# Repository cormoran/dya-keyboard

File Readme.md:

#  DYA Split Keyboard

## Features

- Controller: RP2040-zero (QMK) and XAIO NRF52840 plus (ZMK)
  - ZMK firmware is not available yet, since XAIO NRF52840 plus cannot be used in Japan for now.
- Layout: US and JIS
- Switch: Cherry MX compatible, hotswappable
- LED x 12 (left 4, right 4 + 4 indicator)
- PMW3610 low power trackball sensor
- Optional features by soldering additional parts
  - Lipo battery support for XAIO
  - AAA battery (1.2V NiMH or 1.5V) support

## Build Guide

[V1.0 部品取り付け済み基板（日本語）](./hardware/dya-v1/build-guide/pcba/Readme-ja.md)

## Firmware

Pre-built QMK firmware is available in latest build's artifact section in [this github actions](https://github.com/cormoran/dya-keyboard/actions/workflows/main.yml).

Three binaries (via, us, jis) are zipped in `dya_qmk_latest.zip`. `via` binary supports [VIA](https://www.usevia.app/) and [Remap](https://remap-keys.app/) to change keymapping. Keyboard definition json for VIA is available in [`./firmware/qmk/keybaords/dya/dya-via.json`](https://github.com/cormoran/dya-keyboard/blob/main/firmware/qmk/keyboards/dya/dya-via.json).

## Gallery

- Keycap: [acid-caps](https://keeb-on.com/collections/acid-caps) or no-brand white cap
- Trackball: 34mm

### US Layout setup

#### LED decoration and indicators

### JIS Layout setup

### Schematic

## Shop

Available in https://cormoran707.booth.pm/items/6705756

## License

- QMK firmware (./firmware/qmk_firmware/\*): Inherits its license. Majority of them are under GPLv2. See its own repository.
- DYA logo  (./img/dya.svg): All rights reserved.
- Other keyboard pictures under ./img: CC BY
- Hardware
  - kicad library (./hardware/kicad_library/\*) and sch (\*.kicad_sch): MIT
  - PCB (\*.kicad_pcb): CC BY-NC
  - Case data (\*.stl): CC BY

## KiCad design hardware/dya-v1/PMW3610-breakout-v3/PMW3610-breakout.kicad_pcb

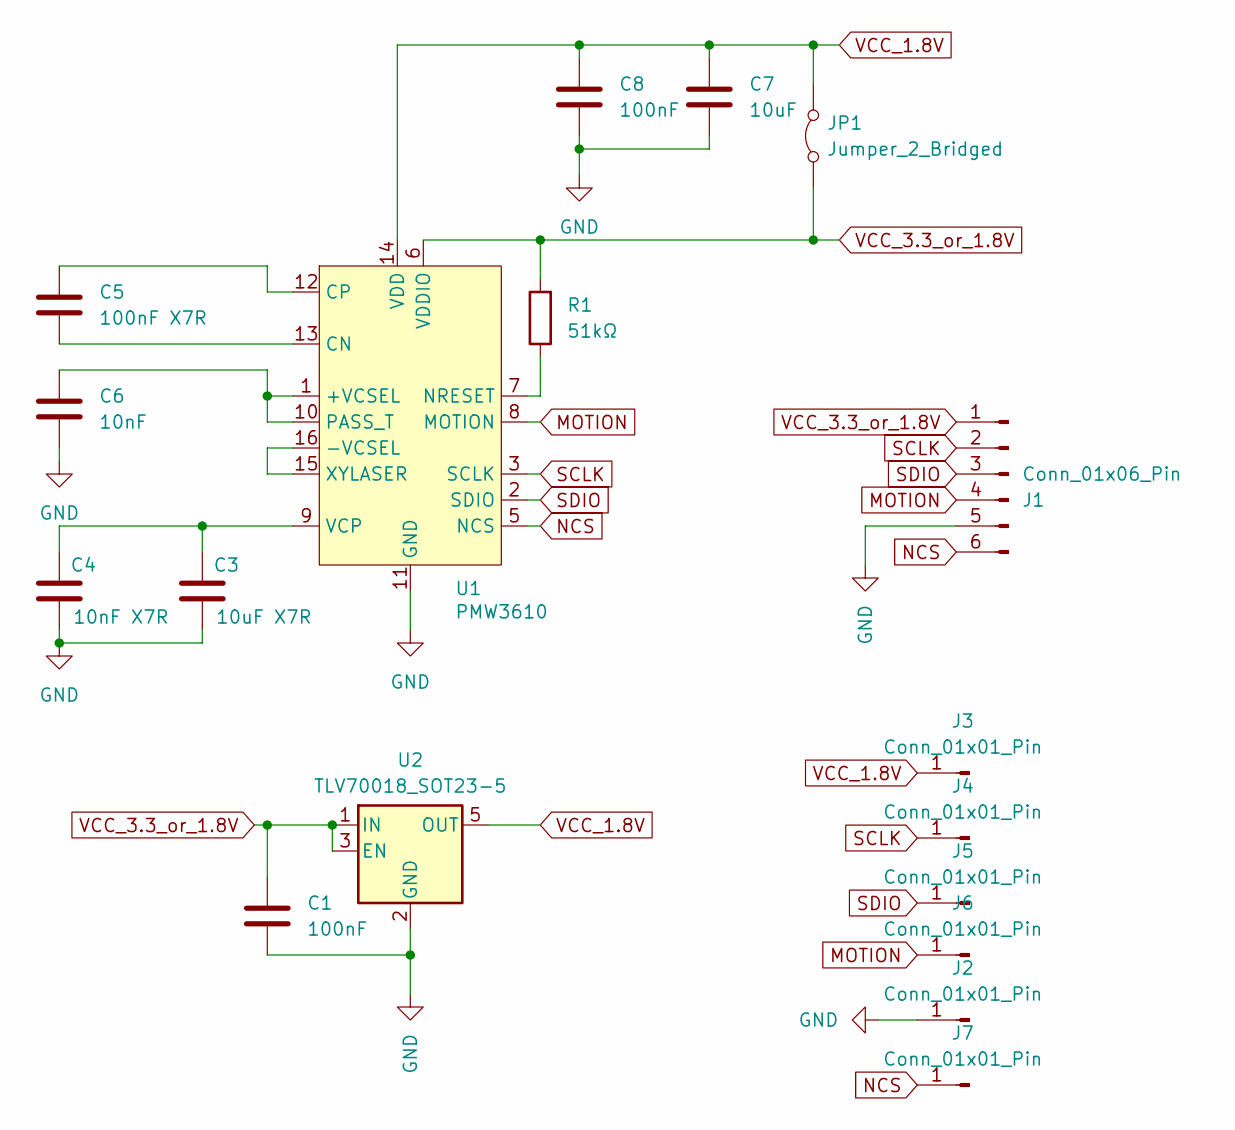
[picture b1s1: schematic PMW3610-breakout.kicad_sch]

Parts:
C1, C8: 100nF; C_0603_1608Metric; LCSC C14663
C3: 10uF X7R; C_0603_1608Metric; LCSC C19702
C4: 10nF X7R; C_0603_1608Metric; LCSC C57112
C5: 100nF X7R; C_0603_1608Metric; LCSC C14663
C6: 10nF; C_0603_1608Metric; LCSC C57112
C7: 10uF; C_0603_1608Metric; LCSC C19702
J1: Conn_01x06_Pin; JUSHUO-AFH34-S06FIA-1H; LCSC C5139821
J2, J3, J4, J5, J6, J7: Conn_01x01_Pin; TestPoint_Pad_D1.0mm
JP1: Jumper_2_Bridged; SolderJumper-2_P1.3mm_Open_RoundedPad1.0x1.5mm
R1: 51kΩ; R_0603_1608Metric; LCSC C23196
U1: PMW3610; PMW3610DM-SUDU 16Pin
U2: TLV70018_SOT23-5; SOT-23-5

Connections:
GND: C1.2, C3.2, C4.2, C6.2, C7.2, C8.2, J1.5, J2.1, U1.11 (GND), U2.2 (GND)
MOTION: J1.4, J6.1, U1.8 (MOTION)
NCS: J1.6, J7.1, U1.5 (NCS)
unnamed: C6.1, U1.1 (+VCSEL), U1.10 (PASS_T)
unnamed: U1.15 (XYLASER), U1.16 (-VCSEL)
unnamed: C5.2, U1.13 (CN)
unnamed: C5.1, U1.12 (CP)
unnamed: R1.1, U1.7 (NRESET)
unnamed: C3.1, C4.1, U1.9 (VCP)
SCLK: J1.2, J4.1, U1.3 (SCLK)
SDIO: J1.3, J5.1, U1.2 (SDIO)
VCC_1.8V: C7.1, C8.1, J3.1, JP1.2 (B), U1.14 (VDD), U2.5 (OUT)
VCC_3.3_or_1.8V: C1.1, J1.1, JP1.1 (A), R1.2, U1.6 (VDDIO), U2.1 (IN), U2.3 (EN)

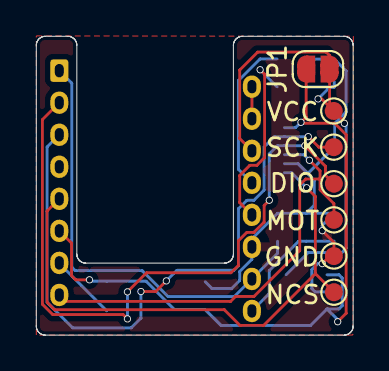
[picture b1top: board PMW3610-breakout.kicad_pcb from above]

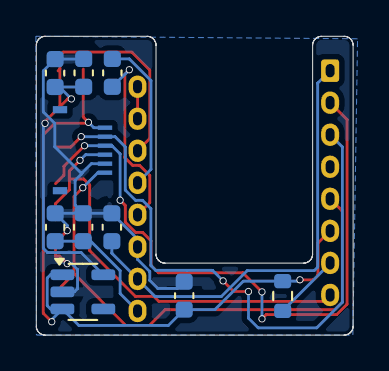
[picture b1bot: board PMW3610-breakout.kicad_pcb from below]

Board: 2 copper layers, 17.6 x 16.6 mm, 18 parts (10 on the bottom side), 13 nets.

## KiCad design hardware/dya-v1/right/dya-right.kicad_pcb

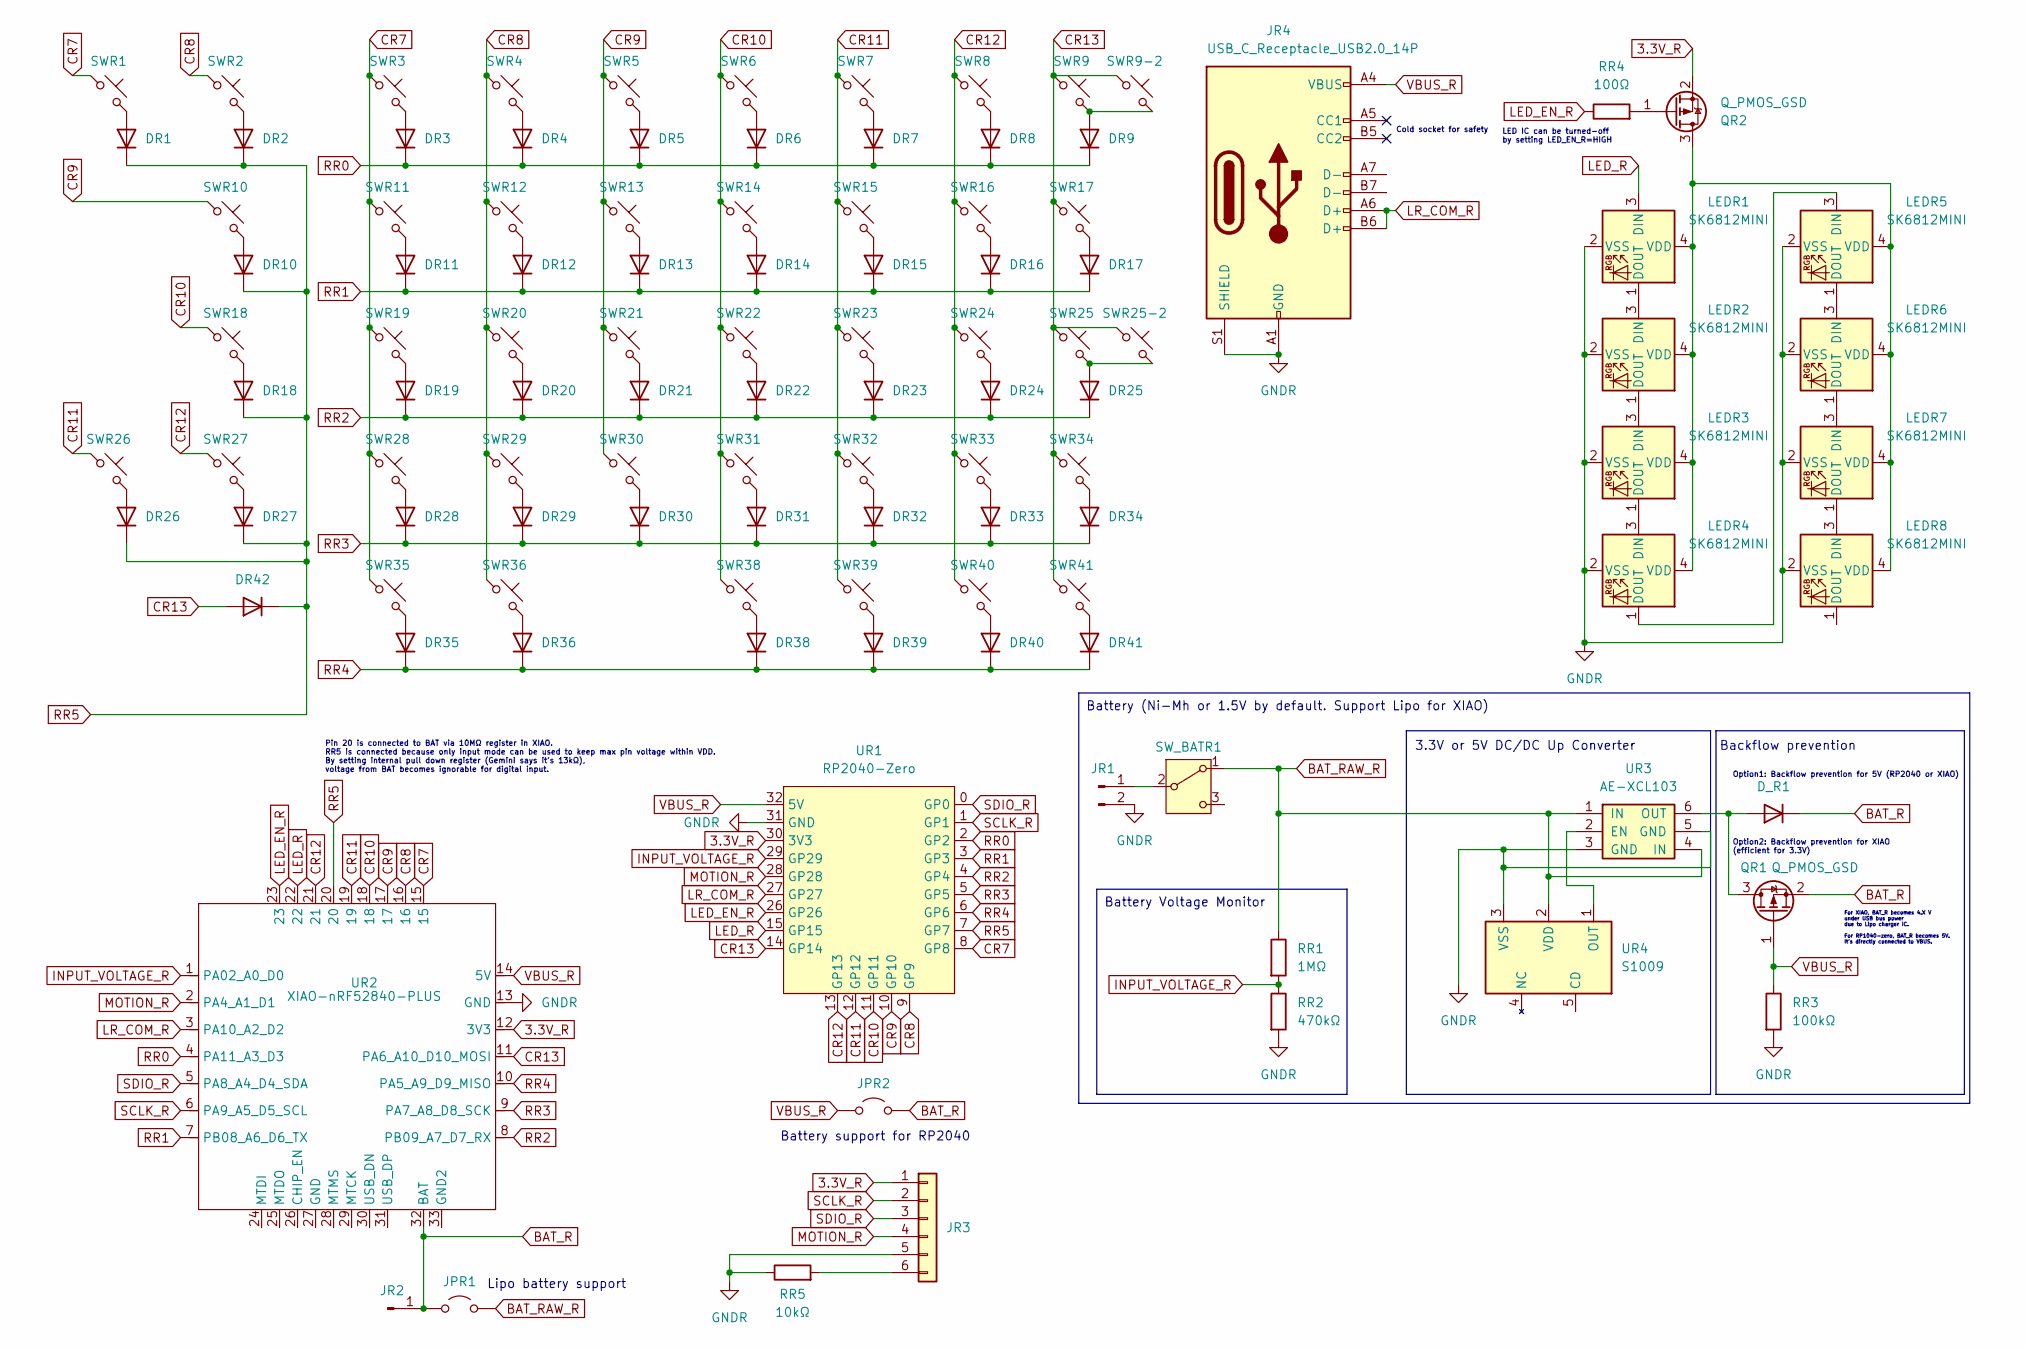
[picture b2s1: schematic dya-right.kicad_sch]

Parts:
DR1, DR2, DR3, DR4, DR5, DR6, DR7, DR8, DR9, DR10, DR11, DR12, DR13, DR14, DR15, DR16, DR17, DR18, DR19, DR20, DR21, DR22, DR23, DR24, DR25, DR26, DR27, DR28, DR29, DR30, DR31, DR32, DR33, DR34, DR35, DR36, DR38, DR39, DR40, DR41, DR42: D; D_SOD-123; LCSC C81598
D_R1: D; D_SOD-123; LCSC C81598
JPR1, JPR2: Jumper_2_Open; SolderJumper-2_P1.3mm_Open_RoundedPad1.0x1.5mm
JR1: Conn_01x02_Pin; JST_ZH_B2B-ZR_1x02_P1.50mm_Vertical
JR2: Conn_01x01_Pin; SolderWirePad_1x01_SMD_1x2mm
JR3: Conn_01x04; JUSHUO-AFH34-S06FIA-1H; LCSC C5139821
JR4: USB_C_Receptacle_USB2.0_14P; USB_C_Receptacle_G-Switch_GT-USB-7010ASV; LCSC C2927038
LEDR1, LEDR2, LEDR3, LEDR4, LEDR5, LEDR6, LEDR7, LEDR8: SK6812MINI; LED_SK6812MINI-E_BL; LCSC C5149201
QR1, QR2: Q_PMOS_GSD; SOT-23; LCSC C15127
RR1: 1MΩ; R_0805_2012Metric; LCSC C17514
RR2: 470kΩ; R_0805_2012Metric; LCSC C17709
RR3: 100kΩ; R_0805_2012Metric; LCSC C149504
RR4: 100Ω; R_0805_2012Metric; LCSC C17408
RR5: 10kΩ; R_0805_2012Metric; LCSC C17414
SWR1, SWR2, SWR3, SWR4, SWR5, SWR6, SWR7, SWR8, SWR9, SWR10, SWR11, SWR12, SWR13, SWR14, SWR15, SWR16, SWR17, SWR18, SWR19, SWR20, SWR21, SWR22, SWR23, SWR24, SWR26, SWR27, SWR28, SWR29, SWR30, SWR31, SWR32, SWR33, SWR34, SWR38, SWR39, SWR40, SWR41: SW_Push_45deg; MX-Hotswap-1U
SWR9-2: SW_Push_45deg; MX-Hotswap-2U
SWR25: SW_Push_45deg; MX-Hotswap-2.25U-ReversedStabilizers
SWR25-2: SW_Push_45deg; MX-Hotswap-ISO
SWR35, SWR36: SW_Push_45deg; MX-KailhChocV2-Hybrid-Hotswap-1U
SW_BATR1: SW_SPDT; TGSW_MSK-12D19
UR1: RP2040-Zero
UR2: XIAO-nRF52840-PLUS; XIAO_nRF52840_plus
UR3: AE-XCL103
UR4: S1009; SOT-23-5

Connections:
3.3V_R: JR3.1, QR2.2 (S), UR1.30 (3V3), UR2.12 (3V3)
BAT_R: D_R1.1 (K), JPR1.1 (A), JPR2.2 (B), JR2.1, QR1.2 (S), UR2.32 (BAT)
BAT_RAW_R: JPR1.2 (B), RR1.1, SW_BATR1.1 (A), UR3.1 (IN), UR3.4 (IN), UR4.2 (VDD)
CR7: SWR1.1, SWR3.1, SWR11.1, SWR19.1, SWR28.1, SWR35.1, UR1.8 (GP8), UR2.15
CR8: SWR2.1, SWR4.1, SWR12.1, SWR20.1, SWR29.1, SWR36.1, UR1.9 (GP9), UR2.16
CR9: SWR5.1, SWR10.1, SWR13.1, SWR21.1, SWR30.1, UR1.10 (GP10), UR2.17
CR10: SWR6.1, SWR14.1, SWR18.1, SWR22.1, SWR31.1, SWR38.1, UR1.11 (GP11), UR2.18
CR11: SWR7.1, SWR15.1, SWR23.1, SWR26.1, SWR32.1, SWR39.1, UR1.12 (GP12), UR2.19
CR12: SWR8.1, SWR16.1, SWR24.1, SWR27.1, SWR33.1, SWR40.1, UR1.13 (GP13), UR2.21
CR13: DR42.2 (A), SWR9.1, SWR9-2.1, SWR17.1, SWR25.1, SWR25-2.1, SWR34.1, SWR41.1, UR1.14 (GP14), UR2.11 (PA6_A10_D10_MOSI)
GNDR: JR1.2, JR3.5, JR4.A1 (GND), JR4.A12 (GND), JR4.B1 (GND), JR4.B12 (GND), JR4.S1 (SHIELD), LEDR1.2 (VSS), LEDR2.2 (VSS), LEDR3.2 (VSS), LEDR4.2 (VSS), LEDR5.2 (VSS), LEDR6.2 (VSS), LEDR7.2 (VSS), LEDR8.2 (VSS), RR2.2, RR3.2, RR5.1, UR1.31 (GND), UR2.13 (GND), UR3.3 (GND), UR3.5 (GND), UR4.3 (VSS)
INPUT_VOLTAGE_R: RR1.2, RR2.1, UR1.29 (GP29), UR2.1 (PA02_A0_D0)
LED_EN_R: RR4.1, UR1.26 (GP26), UR2.23
LED_R: LEDR1.3 (DIN), UR1.15 (GP15), UR2.22
LR_COM_R: JR4.A6 (D+), JR4.B6 (D+), UR1.27 (GP27), UR2.3 (PA10_A2_D2)
MOTION_R: JR3.4, UR1.28 (GP28), UR2.2 (PA4_A1_D1)
unnamed: DR1.2 (A), SWR1.2
unnamed: DR2.2 (A), SWR2.2
unnamed: DR3.2 (A), SWR3.2
unnamed: DR4.2 (A), SWR4.2
unnamed: DR5.2 (A), SWR5.2
unnamed: DR6.2 (A), SWR6.2
unnamed: DR7.2 (A), SWR7.2
unnamed: DR8.2 (A), SWR8.2
unnamed: DR9.2 (A), SWR9.2, SWR9-2.2
unnamed: DR10.2 (A), SWR10.2
unnamed: DR11.2 (A), SWR11.2
unnamed: DR12.2 (A), SWR12.2
unnamed: DR13.2 (A), SWR13.2
unnamed: DR14.2 (A), SWR14.2
unnamed: DR15.2 (A), SWR15.2
unnamed: DR16.2 (A), SWR16.2
unnamed: DR17.2 (A), SWR17.2
unnamed: DR18.2 (A), SWR18.2
unnamed: DR19.2 (A), SWR19.2
unnamed: DR20.2 (A), SWR20.2
unnamed: DR21.2 (A), SWR21.2
unnamed: DR22.2 (A), SWR22.2
unnamed: DR23.2 (A), SWR23.2
unnamed: DR24.2 (A), SWR24.2
unnamed: DR25.2 (A), SWR25.2, SWR25-2.2
unnamed: DR26.2 (A), SWR26.2
unnamed: DR27.2 (A), SWR27.2
unnamed: DR28.2 (A), SWR28.2
unnamed: DR29.2 (A), SWR29.2
unnamed: DR30.2 (A), SWR30.2
unnamed: DR31.2 (A), SWR31.2
unnamed: DR32.2 (A), SWR32.2
unnamed: DR33.2 (A), SWR33.2
unnamed: DR34.2 (A), SWR34.2
unnamed: DR35.2 (A), SWR35.2
unnamed: DR36.2 (A), SWR36.2
unnamed: DR38.2 (A), SWR38.2
unnamed: DR39.2 (A), SWR39.2
unnamed: DR40.2 (A), SWR40.2
unnamed: DR41.2 (A), SWR41.2
unnamed: D_R1.2 (A), QR1.3 (D), UR3.6 (OUT)
unnamed: JR1.1, SW_BATR1.2 (B)
unnamed: JR3.6, RR5.2
unnamed: LEDR1.1 (DOUT), LEDR2.3 (DIN)
unnamed: LEDR1.4 (VDD), LEDR2.4 (VDD), LEDR3.4 (VDD), LEDR4.4 (VDD), LEDR5.4 (VDD), LEDR6.4 (VDD), LEDR7.4 (VDD), LEDR8.4 (VDD), QR2.3 (D)
unnamed: LEDR2.1 (DOUT), LEDR3.3 (DIN)
unnamed: LEDR3.1 (DOUT), LEDR4.3 (DIN)
unnamed: LEDR4.1 (DOUT), LEDR5.3 (DIN)
unnamed: LEDR5.1 (DOUT), LEDR6.3 (DIN)
unnamed: LEDR6.1 (DOUT), LEDR7.3 (DIN)
unnamed: LEDR7.1 (DOUT), LEDR8.3 (DIN)
unnamed: QR2.1 (G), RR4.2
unnamed: UR3.2 (EN), UR4.1 (OUT)
RR0: DR3.1 (K), DR4.1 (K), DR5.1 (K), DR6.1 (K), DR7.1 (K), DR8.1 (K), DR9.1 (K), UR1.2 (GP2), UR2.4 (PA11_A3_D3)
RR1: DR11.1 (K), DR12.1 (K), DR13.1 (K), DR14.1 (K), DR15.1 (K), DR16.1 (K), DR17.1 (K), UR1.3 (GP3), UR2.7 (PB08_A6_D6_TX)
RR2: DR19.1 (K), DR20.1 (K), DR21.1 (K), DR22.1 (K), DR23.1 (K), DR24.1 (K), DR25.1 (K), UR1.4 (GP4), UR2.8 (PB09_A7_D7_RX)
RR3: DR28.1 (K), DR29.1 (K), DR30.1 (K), DR31.1 (K), DR32.1 (K), DR33.1 (K), DR34.1 (K), UR1.5 (GP5), UR2.9 (PA7_A8_D8_SCK)
RR4: DR35.1 (K), DR36.1 (K), DR38.1 (K), DR39.1 (K), DR40.1 (K), DR41.1 (K), UR1.6 (GP6), UR2.10 (PA5_A9_D9_MISO)
RR5: DR1.1 (K), DR2.1 (K), DR10.1 (K), DR18.1 (K), DR26.1 (K), DR27.1 (K), DR42.1 (K), UR1.7 (GP7), UR2.20
SCLK_R: JR3.2, UR1.1 (GP1), UR2.6 (PA9_A5_D5_SCL)
SDIO_R: JR3.3, UR1.0 (GP0), UR2.5 (PA8_A4_D4_SDA)
VBUS_R: JPR2.1 (A), JR4.A4 (VBUS), JR4.A9 (VBUS), JR4.B4 (VBUS), JR4.B9 (VBUS), QR1.1 (G), RR3.1, UR1.32 (5V), UR2.14 (5V)

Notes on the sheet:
Option1: Backflow prevention for 5V (RP2040 or XIAO)
Battery (Ni-Mh or 1.5V by default. Support Lipo for XIAO)
Pin 20 is connected to BAT via 10MΩ register in XIAO. RR5 is connected because only input mode can be used to keep max pin voltage within VDD. By setting internal pull down register (Gemini says it's 13kΩ), voltage from BAT becomes ignorable for digital input.
Cold socket for safety
3.3V or 5V DC/DC Up Converter
For XIAO, BAT_R becomes 4.X V under USB bus power due to Lipo charger IC. For RP1040-zero, BAT_R becomes 5V. It's directly connected to VBUS.
Backflow prevention
Battery support for RP2040
LED IC can be turned-off by setting LED_EN_R=HIGH
Battery Voltage Monitor
Option2: Backflow prevention for XIAO (efficient for 3.3V)
Lipo battery support

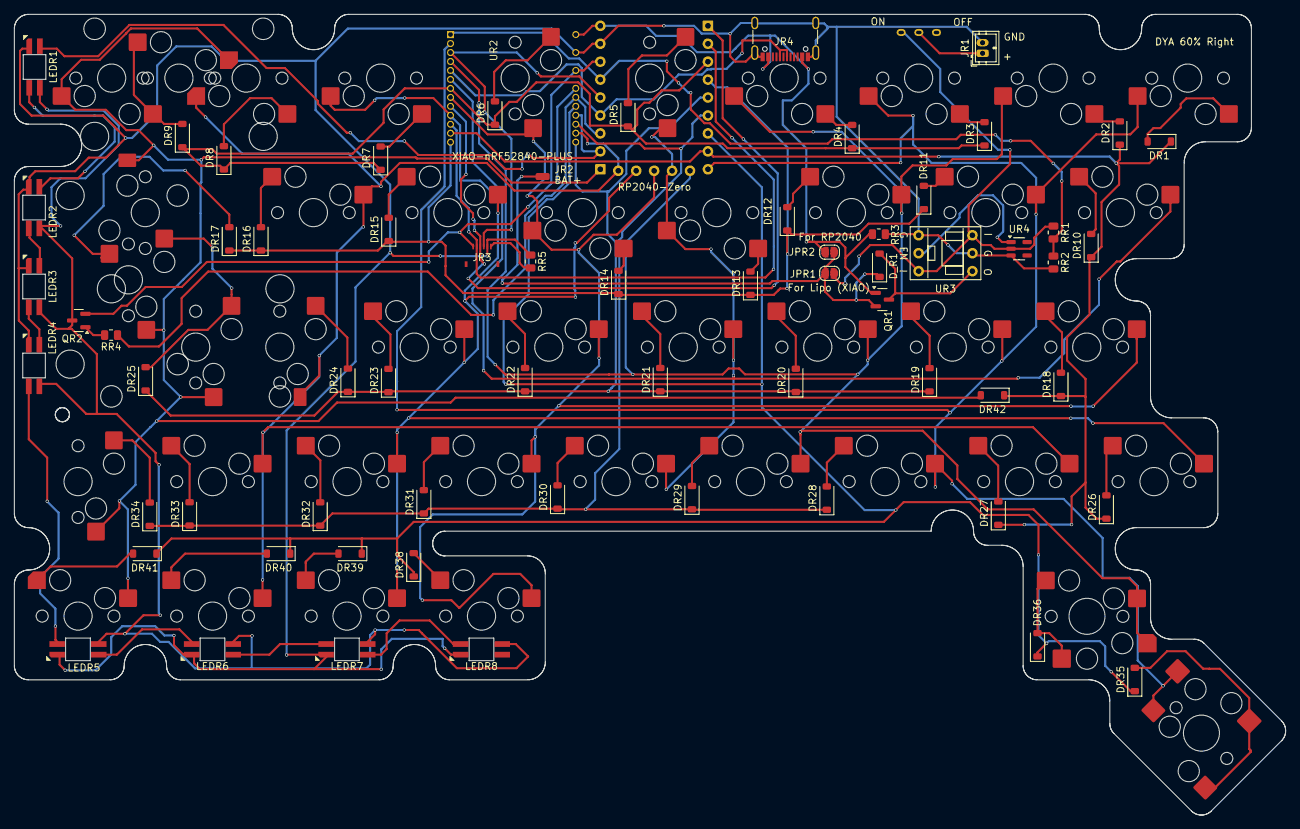
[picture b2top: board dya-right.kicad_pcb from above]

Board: 2 copper layers, 180.1 x 113.4 mm, 110 parts (1 on the bottom side), 78 nets.

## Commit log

2025-03-16 Add build guide
2025-03-16 dark-mode svg
2025-03-18 Add case data
2025-03-20 Add test farms for xiao-nrf52840-plus
2025-03-20 Import qmk farm for dya keyboard
2025-03-21 Support VIA
2025-03-21 Change RGB Light to RGB Matrix
2025-03-21 Add firmware section
2025-03-21 Add farmware guide to build guide
2025-03-21 Add kit contents picture and improve build guide
2025-03-22 Small fix in build guide
2025-03-22 Add booth link and schematic picture
2025-03-22 Add link to keystroke sound.
2025-03-31 Add firmware guide
2025-03-31 rename farm -> firmware
2025-03-31 Fix wrong link
2025-05-17 Improve form-mod build guide
2025-05-18 Fix number of stabilizer for JIS layout
